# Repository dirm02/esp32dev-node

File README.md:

# esp32dev-node
ESP32 + RFM95 LORA Note with OLED Display and Joystick PCB

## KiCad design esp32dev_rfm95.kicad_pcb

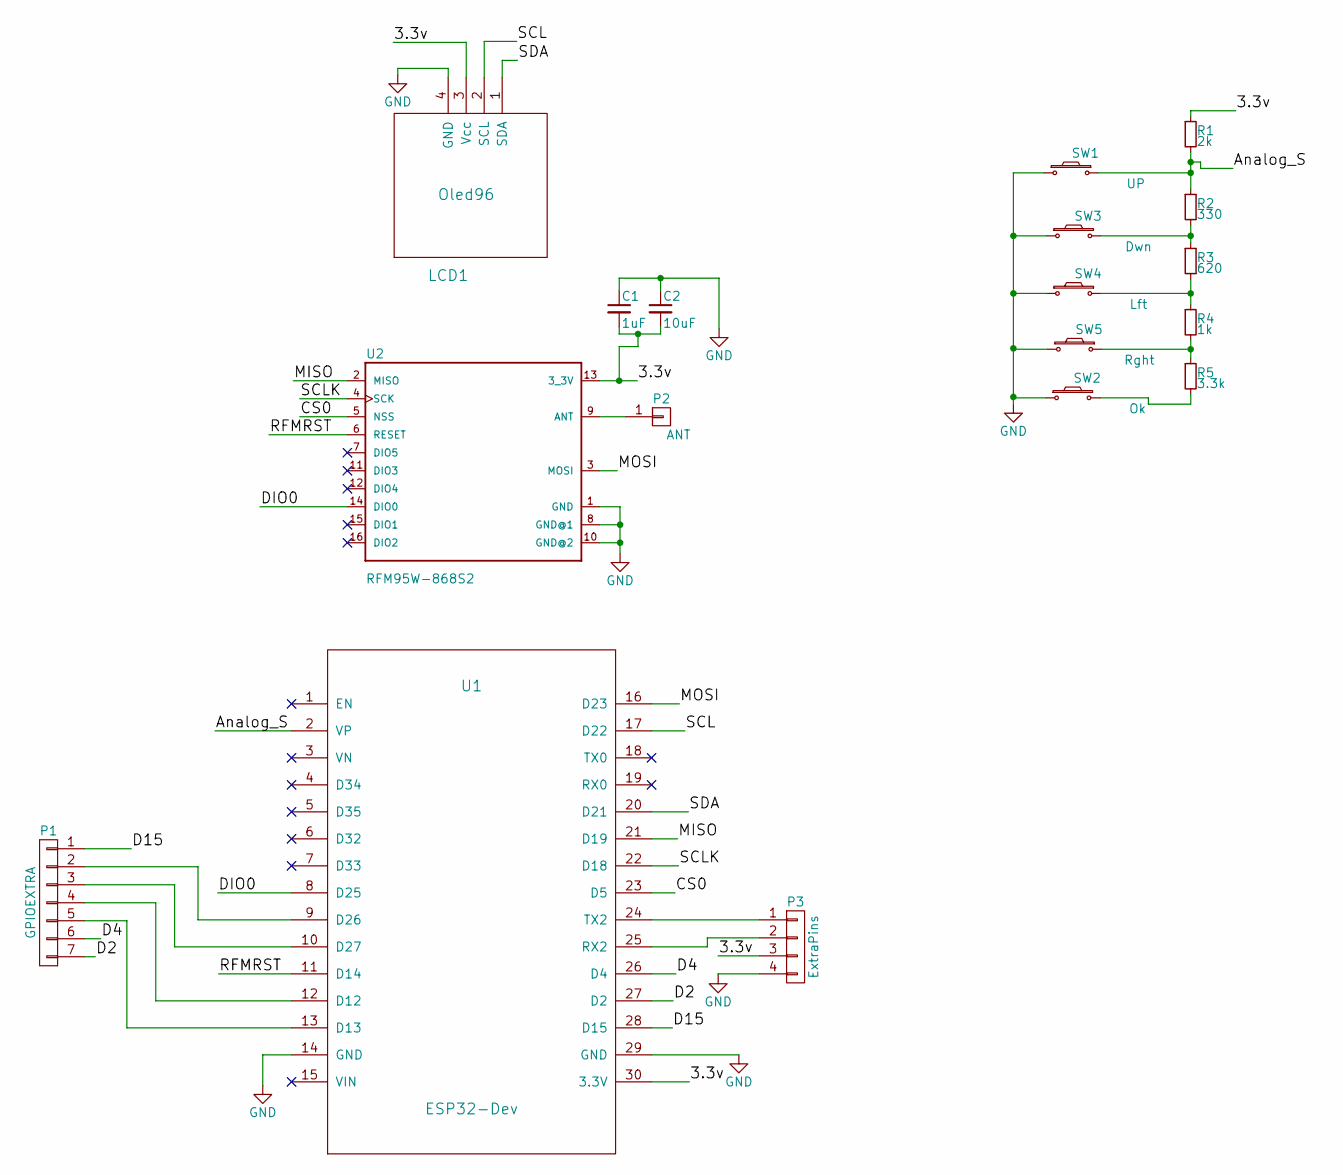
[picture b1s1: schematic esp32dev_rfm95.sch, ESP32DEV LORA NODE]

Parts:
C1: 1uF; C_1206_HandSoldering
C2: 10uF; C_1206_HandSoldering
LCD1: Oled96
P1: GPIOEXTRA; Socket_Strip_Straight_1x07_Pitch2.54mm
P2: ANT; SolderWirePad_single_2-5mmDrill
P3: ExtraPins; Socket_Strip_Straight_1x04_Pitch2.54mm
R1: 2k; R_1206_HandSoldering
R2: 330; R_1206_HandSoldering
R3: 620; R_1206_HandSoldering
R4: 1k; R_1206_HandSoldering
R5: 3.3k; R_1206_HandSoldering
SW1: UP; SW_SPST_B3U-1000P
SW2: Ok; SW_SPST_B3U-1000P
SW3: Dwn; SW_SPST_B3U-1000P
SW4: Lft; SW_SPST_B3U-1000P
SW5: Rght; SW_SPST_B3U-1000P
U1: ESP32-Dev; ESP32-DEV2
U2: RFM95W-868S2; RFM69HW_SMD_Handsoldering

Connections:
/3.3v: C1.2, C2.2, LCD1.3 (Vcc), P3.3, R1.1, U1.30 (3.3V), U2.13 (3_3V)
/Analog_S: R1.2, R2.1, SW1.2, U1.2 (VP)
/CS0: U1.23 (D5), U2.5 (NSS)
/D2: P1.7, U1.27 (D2)
/D4: P1.6, U1.26 (D4)
/D15: P1.1, U1.28 (D15)
/DIO0: U1.8 (D25), U2.14 (DIO0)
/MISO: U1.21 (D19), U2.2 (MISO)
/MOSI: U1.16 (D23), U2.3 (MOSI)
/RFMRST: U1.11 (D14), U2.6 (RESET)
/SCL: LCD1.2 (SCL), U1.17 (D22)
/SCLK: U1.22 (D18), U2.4 (SCK)
/SDA: LCD1.1 (SDA), U1.20 (D21)
GND: C1.1, C2.1, LCD1.4 (GND), P3.4, SW1.1, SW2.1, SW3.1, SW4.1, SW5.1, U1.14 (GND), U1.29 (GND), U2.1 (GND), U2.8 (GND@1), U2.10 (GND@2)
unnamed: P1.2, U1.9 (D26)
unnamed: P1.3, U1.10 (D27)
unnamed: P1.4, U1.12 (D12)
unnamed: P1.5, U1.13 (D13)
unnamed: P2.1, U2.9 (ANT)
unnamed: P3.1, U1.24 (TX2)
unnamed: P3.2, U1.25 (RX2)
unnamed: R2.2, R3.1, SW3.2
unnamed: R3.2, R4.1, SW4.2
unnamed: R4.2, R5.1, SW5.2
unnamed: R5.2, SW2.2

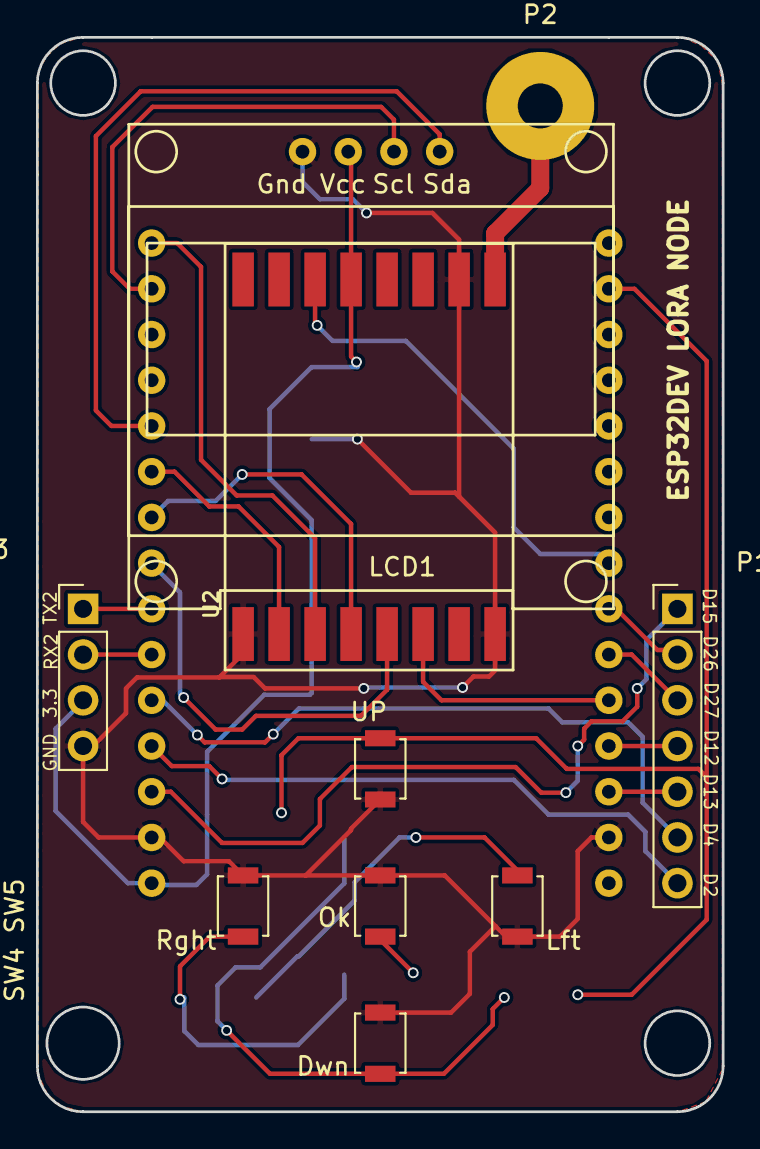
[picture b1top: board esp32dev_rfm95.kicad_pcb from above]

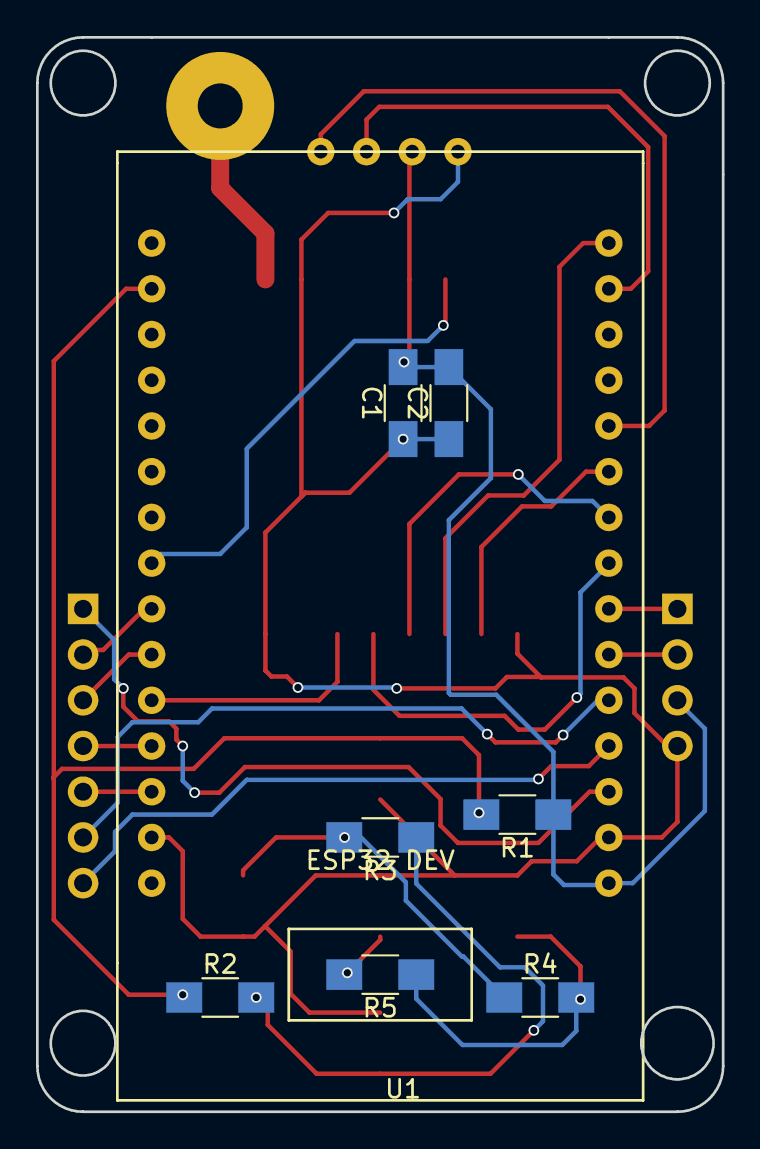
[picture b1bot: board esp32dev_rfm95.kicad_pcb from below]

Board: 2 copper layers, 38.1 x 59.7 mm, 18 parts (8 on the bottom side), 25 nets.
